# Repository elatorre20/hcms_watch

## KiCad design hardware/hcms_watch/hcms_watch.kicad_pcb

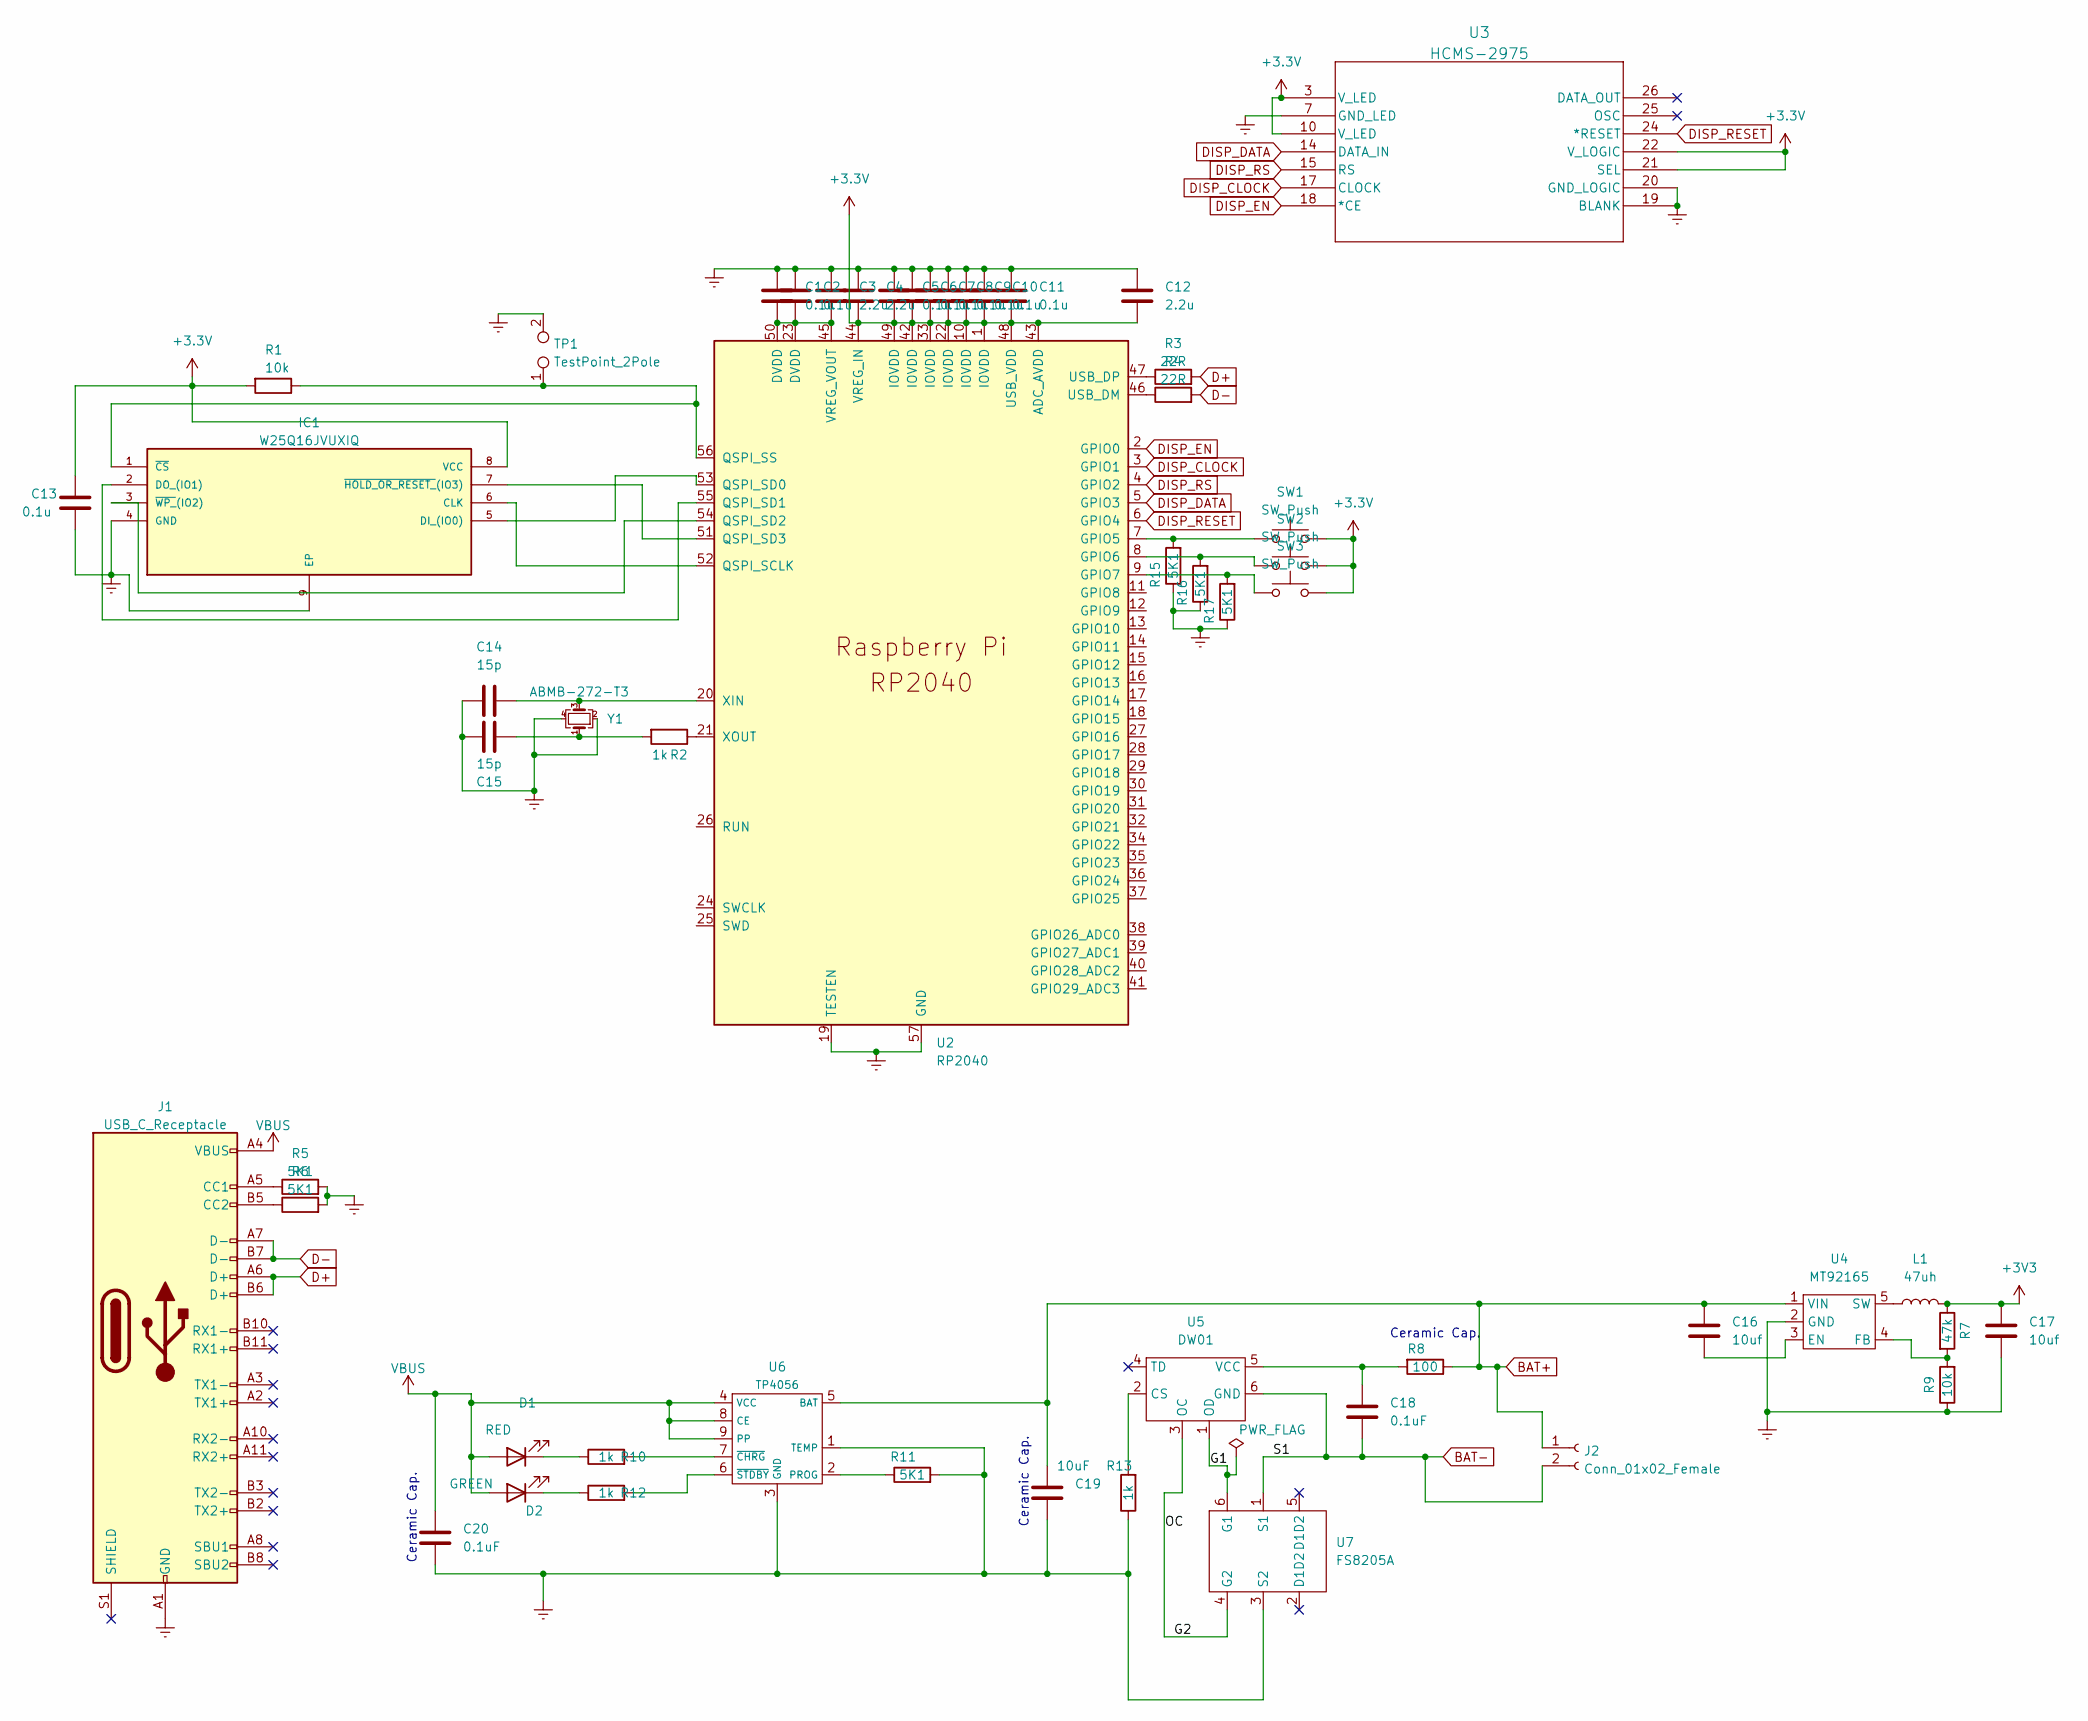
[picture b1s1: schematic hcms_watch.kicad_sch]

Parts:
C1, C2, C5, C6, C7, C8, C9, C10, C11, C13: 0.1u; C_0805_2012Metric
C3, C4, C12: 2.2u; C_0805_2012Metric
C14, C15: 15p; C_0805_2012Metric
C16, C17: 10uf; C_0805_2012Metric
C18, C20: 0.1uF; C_0805_2012Metric
C19: 10uF; C_0805_2012Metric
D1: RED; LED_0805_2012Metric
D2: GREEN; LED_0805_2012Metric
IC1: W25Q16JVUXIQ; SON-8_2x3MM; MANUFACTURER_PART_NUMBER W25Q16JVUXIQ
J1: USB_C_Receptacle; USB_C_Receptacle_XKB_U262-16XN-4BVC11
J2: Conn_01x02_Female; PinHeader_1x02_P2.54mm_Vertical
L1: 47uh; L_Neosid_SMS-ME3015
R1, R9: 10k; R_0805_2012Metric
R2, R10, R12, R13: 1k; R_0805_2012Metric
R3, R4: 22R; R_0805_2012Metric
R5, R6, R11, R15, R16, R17: 5K1; R_0805_2012Metric
R7: 47k; R_0805_2012Metric
R8: 100; R_0805_2012Metric
SW1, SW2, SW3: SW_Push; 6MM_slim_pushbutton
TP1: TestPoint_2Pole; SolderJumper-2_P1.3mm_Open_RoundedPad1.0x1.5mm
U2: RP2040; RP2040-QFN-56
U3: HCMS-2975; DIP26_HCMS-290X-E_BRA
U4: MT92165; SOT-23-5
U5: DW01; SOT-23-6_Handsoldering
U6: TP4056; SOIC-8-1EP_3.9x4.9mm_P1.27mm_EP2.29x3mm
U7: FS8205A; SOT-23-6_Handsoldering
Y1: ABMB-272-T3; Crystal_SMD_3225-4Pin_3.2x2.5mm

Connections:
/G1: U5.1 (OD), U7.6 (G1)
BAT+: C16.1, C19.1, J2.1, R8.1, U4.1 (VIN), U6.5 (BAT)
BAT-: C18.2, J2.2, U5.6 (GND), U7.1 (S1)
D+: J1.A6 (D+), J1.B6 (D+), R3.2
D-: J1.A7 (D-), J1.B7 (D-), R4.2
DISP_CLOCK: U2.3 (GPIO1), U3.17 (CLOCK)
DISP_DATA: U2.5 (GPIO3), U3.14 (DATA_IN)
DISP_EN: U2.2 (GPIO0), U3.18 (*CE)
DISP_RESET: U2.6 (GPIO4), U3.24 (*RESET)
DISP_RS: U2.4 (GPIO2), U3.15 (RS)
Earth: C1.1, C2.1, C3.1, C4.1, C5.1, C6.1, C7.1, C8.1, C9.1, C10.1, C11.1, C12.1, C13.1, C14.2, C15.2, C17.2, C19.2, C20.2, IC1.4 (GND), IC1.9 (EP), J1.A1 (GND), J1.A12 (GND), J1.B1 (GND), J1.B12 (GND), R5.2, R6.2, R9.1, R11.2, R13.1, R15.1, R16.1, R17.1, TP1.2, U2.19 (TESTEN), U2.57 (GND), U3.7 (GND_LED), U3.19 (BLANK), U3.20 (GND_LOGIC), U4.2 (GND), U6.1 (TEMP), U6.3 (GND), U7.3 (S2), Y1.2, Y1.4
unnamed: C1.2, C2.2, C3.2, U2.23 (DVDD), U2.45 (VREG_VOUT), U2.50 (DVDD)
unnamed: C14.1, U2.20 (XIN), Y1.3
unnamed: C15.1, R2.2, Y1.1
unnamed: C16.2, U4.3 (EN)
unnamed: C18.1, R8.2, U5.5 (VCC)
unnamed: D1.1 (K), R10.1
unnamed: D2.1 (K), R12.1
unnamed: J1.A5 (CC1), R5.1
unnamed: J1.B5 (CC2), R6.1
unnamed: L1.1, U4.5 (SW)
unnamed: IC1.1 (~CS), R1.1, TP1.1, U2.56 (QSPI_SS)
unnamed: R2.1, U2.21 (XOUT)
unnamed: R7.2, R9.2, U4.4 (FB)
unnamed: R10.2, U6.7 (~CHRG)
unnamed: R11.1, U6.2 (PROG)
unnamed: R12.2, U6.6 (~STDBY)
unnamed: R13.2, U5.2 (CS)
unnamed: R15.2, SW1.1, U2.7 (GPIO5)
unnamed: R16.2, SW2.1, U2.8 (GPIO6)
unnamed: R17.2, SW3.1, U2.9 (GPIO7)
unnamed: R4.1, U2.46 (USB_DM)
unnamed: R3.1, U2.47 (USB_DP)
unnamed: IC1.7 (~HOLD_OR_RESET_(IO3)), U2.51 (QSPI_SD3)
unnamed: IC1.6 (CLK), U2.52 (QSPI_SCLK)
unnamed: IC1.5 (DI_(IO0)), U2.53 (QSPI_SD0)
unnamed: IC1.3 (~WP_(IO2)), U2.54 (QSPI_SD2)
unnamed: IC1.2 (DO_(IO1)), U2.55 (QSPI_SD1)
VBUS: C20.1, D1.2 (A), D2.2 (A), J1.A4 (VBUS), J1.A9 (VBUS), J1.B4 (VBUS), J1.B9 (VBUS), U6.4 (VCC), U6.8 (CE), U6.9 (PP)

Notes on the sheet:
Ceramic Cap.

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
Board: 4 copper layers, 54 parts (9 on the bottom side), 42 nets, no tracks yet.

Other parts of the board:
R14: 0R; R_0805_2012Metric

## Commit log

2024-07-04 Added serial print sketch
    There is a weird crash in the onboard usb serial port. I am 98% certain that this is because of some resource issue and not a formal fault in the code. Will have to look into this further.
2024-07-04 Created basic clock code
    Basic outline of clock code. Keeps track of time and prints it in hh:mm:ss on the screen. Will add provisions for updating time and showing date through buttons.
2024-07-04 2-line option
    Added version with 2 lines for date as well as time. will begin working on adjustment through buttons.
2024-07-05 Finished time adjustment code
    Added button adjustment for time and date and mode button to display date.
2024-08-27 Starting on board design
    Laid out the board and placed the large components. Moving on to routing the caps/resistors.
